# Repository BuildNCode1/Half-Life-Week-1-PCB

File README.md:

# Unghost
> A pocket-sized reminder device that nudges you to reach out to the people you haven't talked to in a while.

## Why I made this
Isolation is too common in today's culture. With everyone rushing to the next task of a busy life, everyday human contact can be left all but forgotten. This little guy fixes that, and makes keeping in touch harder to forget.

## What it does

- Tracks how long it's been since you contacted each person
- Chimes with a little "waka waka" when someone is overdue
- Shows the contacts, days since last contact, and a "Call (So and Such)!" banner on an OLED
- Three buttons: **Next contact**, **I contacted them**, **Snooze**
- Shows room temperature and humidity
- *(PLANNED)* Syncs contacts and time from your phone over Bluetooth LE

## Hardware

| Part | Purpose | Link to Part|
|---|---|---|
| Seeed XIAO ESP32-C3 | Microcontroller with built-in BLE | https://www.aliexpress.us/item/3256813149598103.html?spm=a2g0o.productlist.main.31.72e51b27ticEIA&utparam-url=scene%3Asearch%7Cquery_from%3Apc_back_same_best%7Cx_object_id%3A1005013335912855%7C_p_origin_prod%3A&algo_pvid=fac4086b-41df-4410-8774-2cec6717ea30&algo_exp_id=fac4086b-41df-4410-8774-2cec6717ea30&pdp_ext_f=%7B%22order%22%3A%226%22%2C%22fromPage%22%3A%22search%22%7D&pdp_npi=6%40dis%21USD%217.89%217.89%21%21%2152.58%2152.58%21%4021032c8d17917436391875521e138e%2112000060888678592%21sea%21US%218282866592%21ABX%211%210%21n_tag%3A-29910%3Bd%3A5aa8ee6%3Bm03_new_user%3A-29895&gatewayAdapt=4itemAdapt |
| 0.96" SSD1306 OLED (I2C) | Display | https://www.aliexpress.us/item/3256807526105550.html?src=google&gatewayAdapt=glo2usa |
| MPU6050 breakout | Motion sensing | https://www.aliexpress.us/item/3256809542137777.html?spm=a2g0o.productlist.main.16.23d038f2i6RvNN&aem_p4p_detail=202610090934522322066556534280001064859&algo_pvid=fe07dd36-d839-4601-9284-38ed574bb029&algo_exp_id=fe07dd36-d839-4601-9284-38ed574bb029-15&pdp_ext_f=%7B%22order%22%3A%22265%22%2C%22eval%22%3A%221%22%2C%22fromPage%22%3A%22search%22%7D&pdp_npi=6%40dis%21USD%212.54%211.09%21%21%2116.90%217.24%21%402101c4ea17915636923421634e0e05%2112000049970912779%21sea%21US%210%21ABX%211%210%21n_tag%3A-29910%3Bd%3A5aa8ee6%3Bm03_new_user%3A-29895%3BpisId%3A5000000210792318&curPageLogUid=ynQDqgGyoUWL&utparam-url=scene%3Asearch%7Cquery_from%3A%7Cx_object_id%3A1005009728452529%7C_p_origin_prod%3A&search_p4p_id=202610090934522322066556534280001064859_5 |
| DHT11 | Temperature and Humidity | https://www.aliexpress.us/item/3256807449697831.html?spm=a2g0o.productlist.main.25.115d71f3f5ViME&utparam-url=scene%3Asearch%7Cquery_from%3Apc_back_same_best%7Cx_object_id%3A1005007636012583%7C_p_origin_prod%3A1005007728845619&algo_pvid=f96a3c48-c252-4dc3-beaa-f8c6c141981a&algo_exp_id=f96a3c48-c252-4dc3-beaa-f8c6c141981a&pdp_ext_f=%7B%22order%22%3A%223403%22%2C%22orig_sl_item_id%22%3A%221005007636012583%22%2C%22orig_item_id%22%3A%221005007728845619%22%2C%22fromPage%22%3A%22search%22%7D&pdp_npi=6%40dis%21USD%213.26%211.57%21%21%2121.70%2110.42%21%402101ca9517915638798716403e13fe%2112000060728245105%21sea%21US%210%21ABX%211%210%21n_tag%3A-29910%3Bd%3A5aa8ee6%3Bm03_new_user%3A-29895&gatewayAdapt=4itemAdapt |
| Passive piezo buzzer | Reminder chimes | https://www.aliexpress.us/item/3256808937377909.html?spm=a2g0o.productlist.main.15.23ef3ebdlbdhYI&algo_pvid=34c48f26-0c36-409c-a233-be8ad6a0c4f5&algo_exp_id=34c48f26-0c36-409c-a233-be8ad6a0c4f5-14&pdp_ext_f=%7B%22order%22%3A%2224%22%2C%22eval%22%3A%221%22%2C%22fromPage%22%3A%22search%22%7D&pdp_npi=6%40dis%21USD%2114.77%211.09%21%21%2198.43%217.32%21%4021030f4a17915639639967313e0cc7%2112000048231116217%21sea%21US%210%21ABX%211%210%21n_tag%3A-29910%3Bd%3A5aa8ee6%3Bm03_new_user%3A-29895%3BpisId%3A5000000218165385&curPageLogUid=RCSgW0AXWaw7&utparam-url=scene%3Asearch%7Cquery_from%3A%7Cx_object_id%3A1005009123692661%7C_p_origin_prod%3A |
| 3× Cherry MX Switches | User Input | https://www.aliexpress.us/item/2255800623836900.html?spm=a2g0o.productlist.main.1.72dd48adaWgnvN&algo_pvid=b974df5a-dc4d-4cb8-b9ca-c856ea2fe168&algo_exp_id=b974df5a-dc4d-4cb8-b9ca-c856ea2fe168-0&pdp_ext_f=%7B%22order%22%3A%22130%22%2C%22eval%22%3A%221%22%2C%22fromPage%22%3A%22search%22%7D&pdp_npi=6%40dis%21USD%218.18%211.09%21%21%218.18%211.09%21%402101ea8f17915643981201175e0dd8%2110000008113839996%21sea%21US%210%21ABX%211%210%21n_tag%3A-29910%3Bd%3A5aa8ee6%3Bm03_new_user%3A-29895%3BpisId%3A5000000218165385&curPageLogUid=Zb0jw0FzjgCO&utparam-url=scene%3Asearch%7Cquery_from%3A%7Cx_object_id%3A4000810151652%7C_p_origin_prod%3A |
| 10 kΩ resistor (R1) | DHT11 data pull-up | https://www.aliexpress.us/item/3256807353528247.html?spm=a2g0o.productlist.main.1.61eb26c0hKpGF9&algo_pvid=0c864479-b82e-463b-a146-43a65442b576&algo_exp_id=0c864479-b82e-463b-a146-43a65442b576-0&pdp_ext_f=%7B%22order%22%3A%2217685%22%2C%22eval%22%3A%221%22%2C%22orig_sl_item_id%22%3A%221005007539842999%22%2C%22orig_item_id%22%3A%221005006898731441%22%2C%22fromPage%22%3A%22search%22%7D&pdp_npi=6%40dis%21USD%212.15%211.03%21%21%2114.34%216.88%21%402103128917915645394841214e1020%2112000041213434135%21sea%21US%210%21ABX%211%210%21n_tag%3A-29910%3Bd%3A5aa8ee6%3Bm03_new_user%3A-29895&curPageLogUid=seGcnUdWfxei&utparam-url=scene%3Asearch%7Cquery_from%3A%7Cx_object_id%3A1005007539842999%7C_p_origin_prod%3A1005006898731441 |
| 100 Ω resistor (R2) | Buzzer series resistor | https://www.aliexpress.us/item/3256807353528247.html?spm=a2g0o.productlist.main.1.61eb26c0hKpGF9&algo_pvid=0c864479-b82e-463b-a146-43a65442b576&algo_exp_id=0c864479-b82e-463b-a146-43a65442b576-0&pdp_ext_f=%7B%22order%22%3A%2217685%22%2C%22eval%22%3A%221%22%2C%22orig_sl_item_id%22%3A%221005007539842999%22%2C%22orig_item_id%22%3A%221005006898731441%22%2C%22fromPage%22%3A%22search%22%7D&pdp_npi=6%40dis%21USD%212.15%211.03%21%21%2114.34%216.88%21%402103128917915645394841214e1020%2112000041213434135%21sea%21US%210%21ABX%211%210%21n_tag%3A-29910%3Bd%3A5aa8ee6%3Bm03_new_user%3A-29895&curPageLogUid=seGcnUdWfxei&utparam-url=scene%3Asearch%7Cquery_from%3A%7Cx_object_id%3A1005007539842999%7C_p_origin_prod%3A1005006898731441 |

## Pinout
| XIAO Pin | Connected to |
|---|---|
| D1 | DHT11 data |
| D2 | SW1 (next contact) |
| D3 | SW2 (I contacted them) |
| D4 | SW3 (snooze) |
| D5 | I2C SCL |
| D6 | I2C SDA |
| D10 | Buzzer (via 100 Ω) |

## UPDATE
>Just finished designing and uploading the case along with some custom keycaps!

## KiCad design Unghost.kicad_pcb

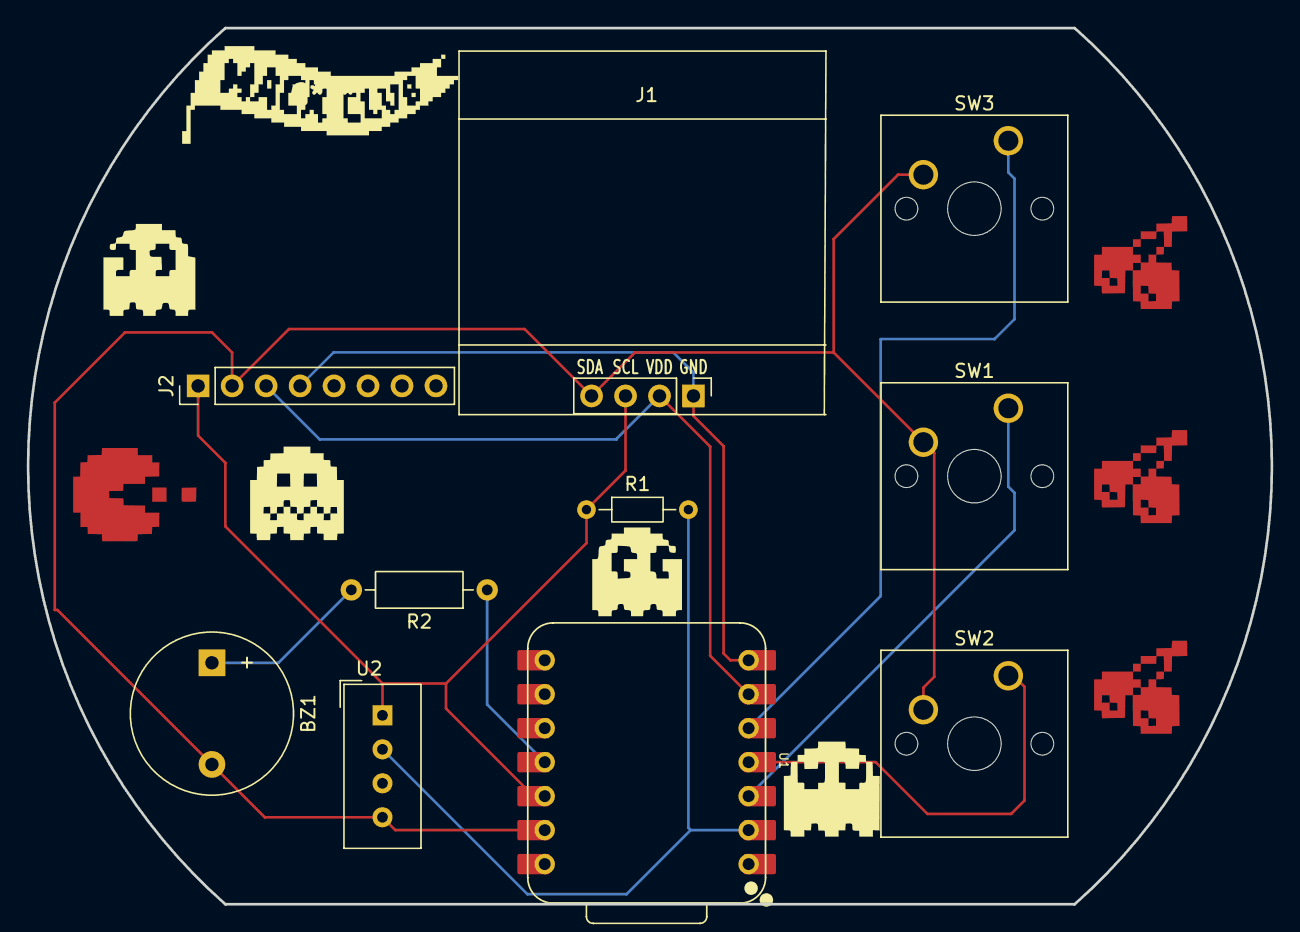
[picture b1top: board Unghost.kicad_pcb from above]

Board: 2 copper layers, 93.0 x 65.5 mm, 10 parts (0 on the bottom side), 10 nets.

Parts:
BZ1: Buzzer; Buzzer_12x9.5RM7.6
J1: Conn_01x04_Pin; Display_128x64_096_I2C
J2: Conn_01x08_Pin; PinHeader_1x08_P2.54mm_Vertical
R1: 10k; R_Axial_DIN0204_L3.6mm_D1.6mm_P7.62mm_Horizontal
R2: 100Ω; R_Axial_DIN0207_L6.3mm_D2.5mm_P10.16mm_Horizontal
SW1, SW2, SW3: SW_Push; SW_Cherry_MX_1.00u_PCB
U1: XIAO-ESP32-C3-SMD; XIAO-ESP32-C6-DIP
U2: DHT11; Aosong_DHT11_5.5x12.0_P2.54mm

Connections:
+3.3V: J1.3, J2.1, R1.1, U1.12 (3V3_OUT), U2.1 (VDD)
/DHT11 DATA: R1.2, U1.2 (D1), U2.2 (DATA)
/GP102: SW1.1, U1.3 (D2)
/GP103: SW2.1, U1.4 (D3)
/GP104: SW3.1, U1.5 (D4)
/GP1010: R2.1, U1.11 (D10)
/SCL: J1.2, J2.3, U1.6 (D5)
/SDA: J1.1, J2.4, U1.7 (D6)
GND: BZ1.2 (-), J1.4, J2.2, SW1.2, SW2.2, SW3.2, U1.13 (GND), U2.4 (GND)
unnamed: BZ1.1 (+), R2.2
